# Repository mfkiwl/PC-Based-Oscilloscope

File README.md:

# Circuit_Design
Eagle Design files, PCB Files, Simulation and Modelling etc.

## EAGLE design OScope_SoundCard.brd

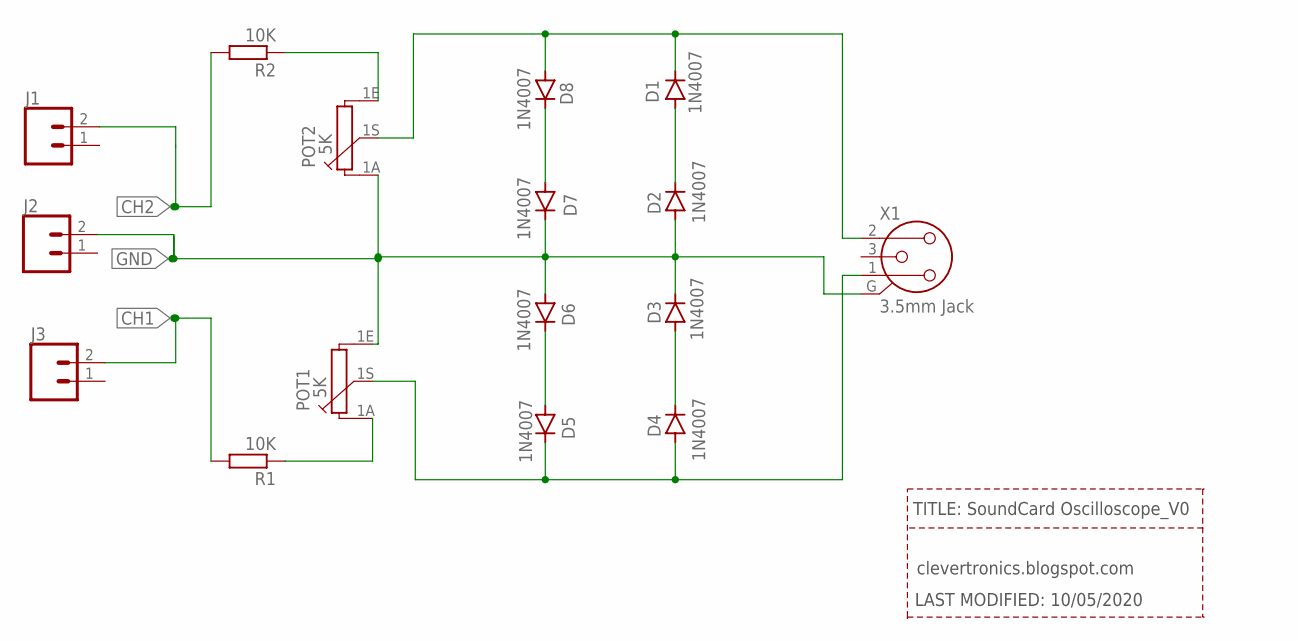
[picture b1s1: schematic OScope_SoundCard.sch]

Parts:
D1, D2, D3, D4, D5, D6, D7, D8: 1N4007; DO41-10
J1, J2, J3: CONN_023.5MM; SCREWTERMINAL-3.5MM-2
POT1, POT2: 5K; PC16S
R1, R2: 10K; 0207/10
X1: 3.5mm Jack; NC3FAH2

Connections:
CH1: J3.2, R1.2
CH2: J1.2, R2.2
unnamed: D5.A, D6.C
unnamed: D3.A, D4.C
unnamed: D4.A, D5.C, POT1.1S, X1.1 (2)
unnamed: D2.A, D3.C, D6.A, D7.C, J2.2, POT1.1E, POT2.1A, X1.G
unnamed: D7.A, D8.C
unnamed: D1.A, D2.C
unnamed: D1.C, D8.A, POT2.1S, X1.2 (1)
unnamed: POT1.1A, R1.1
unnamed: POT2.1E, R2.1

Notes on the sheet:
TITLE: SoundCard Oscilloscope_V0
LAST MODIFIED: 10/05/2020
clevertronics.blogspot.com

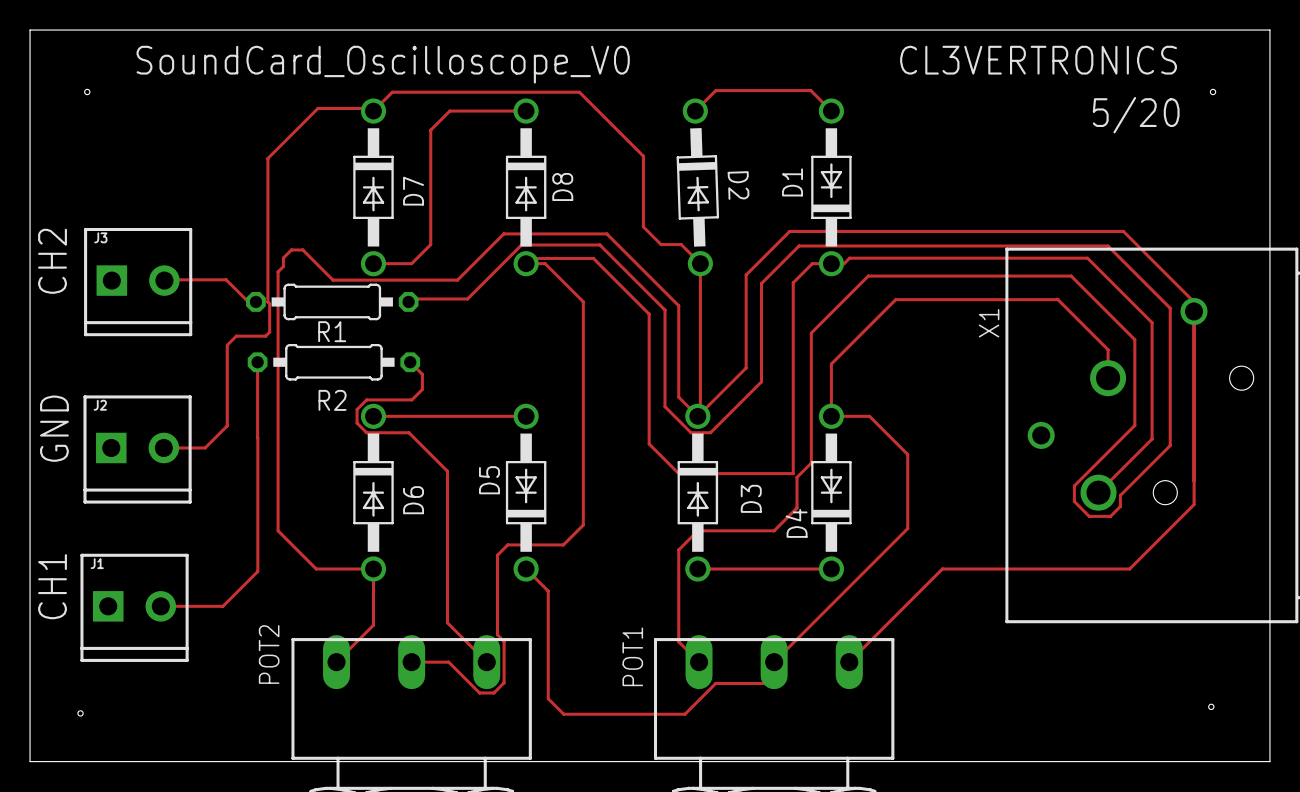
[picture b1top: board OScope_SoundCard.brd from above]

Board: 2 copper layers, 82.5 x 48.7 mm, 16 parts (0 on the bottom side), 11 nets.

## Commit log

2020-05-10 PC Based Oscilloscope files added!

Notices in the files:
parts and their libraries:
SparkFun-Connectors: Licensing: Creative Commons ShareAlike 4.0 International - https://creativecommons.org/licenses/by-sa/4.0
